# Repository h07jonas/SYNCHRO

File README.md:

SYNCHRO
System for Yielding Networked CHannel Rail Operation
SYNCHRO is a modular, high-performance digital model railroad control ecosystem architecture based on the DCC (Digital Command Control) standard. Designed for robust deployment and high signal integrity, the system strictly separates timing and network logic from high-power distribution. Key design pillars include deterministic signal generation, total galvanic isolation to prevent ground loops, and autonomous hardware-level fault management.

System Architecture
The ecosystem is decoupled into three primary hardware modules, allowing independent scaling of logic processing, track driving power, and distributed accessory control.

              +-----------------------------------+
              |      SYNCHRO_Zentrale (MCU)       |
              |  - Timing, Protocol & Networking  |
              +-----------------------------------+
                                |
                                v (Logic Signal / Differential)
              +-----------------------------------+
              |      SYNCHRO_Booster (Power)      |
              |  - Galvanic Isolation (6N137)     |
              |  - Power H-Bridge & Short Control |
              +-----------------------------------+
                                |
                                v (14V DCC Track Power)
              +-----------------------------------+
              |        SYNCHRO_Modul (Acc.)       |
              |  - Signal Monitoring & Decoding   |
              |  - Inductive Load Drivers         |
              +-----------------------------------+
1. Control Unit (SYNCHRO_Zentrale)
The core processing hub handles the network stack, user interface routing, and precision generation of the digital DCC packet stream. It operates entirely on low-voltage logic levels with no direct track-driving capabilities to protect processing assets.

Core Processor: ESP32-S3 microcontroller utilizing its hardware Remote Control (RMT) peripheral engine. This configuration guarantees jitter-free, deterministic DCC bit-timing through dedicated hardware channels, leaving the dual-core CPU free to handle concurrent Wi-Fi, network protocols, and application layer connectivity.

Signal Integrity: Integrated high-speed bus drivers and differential level shifters (MAX485 / 74AHCT125) ensure noise-immune, differential transmission of the logic stream across longer cables to downstream power boosters.

Connectivity: Native USB-C interface providing USB-to-UART bridging for active monitoring, high-rate firmware flashing, and interfacing with industry-standard PC-based railroad command software.

2. Power Booster (SYNCHRO_Booster)
The power-amplification stage isolates the sensitive low-voltage logic signals coming from the Control Unit, scales the voltage rail, and manages high-current output zones to safely drive individual track blocks.

Galvanic Isolation: High-speed 6N137 optocouplers completely break the ground loops between the upstream logic reference ground and the high-current track power ground, preventing destructive feedback currents.

Power Stage: Integrated Full H-Bridge driver (L6203 or discrete N-channel MOSFET bridge layout) optimized to switch high currents at standard track voltages (14V targeted specifically for N-scale layout compliance).

Autonomous Overcurrent Protection: A high-speed hardware-level short-circuit protection loop combining a precision low-side shunt resistor and an analog LM393 comparator. This safety mechanism achieves sub-millisecond latching shutdown independently of MCU firmware involvement, preventing thermal runaway during track shorts.

3. Peripheral Module (SYNCHRO_Modul)
An accessory and function decoder designed to directly tap and monitor the active 14V DCC data stream from the rails, extracting configuration commands to actuate turnouts, mechanical servos, or signal arrays.

Logic Processing: Cost-optimized microcontrollers (ESP32-C3 or ATtiny architectures) coupled with an isolated input filtering stage optimized for reliable track-packet decoding under harsh electronic environments.

Output Driver: High-density, multi-channel Darlington/DMOS transistor arrays (TBD62083AFG / ULN2803A) equipped with integrated clamp diodes to safely absorb inductive flyback voltages generated by heavy turnout switch coils.

Interface Matrix: Universal pin headers and robust terminal blocks customizable via firmware configurations to run solenoid matrix turnouts, static LED signaling displays, or PWM-driven RC servos.

Repository Structure
The directory tree is split logically into engineering domains to facilitate clean version control and modular updates via the graphical Antigravity 2 interface.

SYNCHRO/
├── .gitignore                      # Top-level filter for KiCad/IDE artifacts
├── README.md                       # Core system documentation
├── git_universal_manager.ps1       # Antigravity 2 - Engine
├── Start_Universal_Git_Manager.bat # Antigravity 2 - Launcher
├── Datasheets/                     # Electronic component documentation
├── Docs/                           # System specifications and schematics
├── Software/                       # Source code (Firmware, Apps)
└── Hardware/                       # Electronic Design Automation (EDA)
├── SYNCHRO_Booster/            # KiCad files for Power Booster
├── SYNCHRO_Zentrale/           # KiCad files for Control Unit
└── SYNCHRO_Modul/              # KiCad files for Accessory Decoder

Hardware Development & CAD Rules
All schematics and PCB designs are standardized on KiCad. To prevent repository bloating and synchronization conflicts, adhere strictly to the following tracking protocols:

Versioned Files
*.kicad_pro — Project tracking configurations.

*.kicad_sch — Schematic design worksheets (modular sheet hierarchies are preferred).

*.kicad_pcb — Board layout designs (S-Expression plain text files optimized for line-by-line git diff operations).

Ignored Assets
Local working state files (.kicad_prl), automated schematic backups (-backups/, *.bak), and local editor history configurations (.history/) are systematically excluded via the global .gitignore.

Production assets (Gerber photo-plots, NC drill coordinates, IPC-D-356 netlists, and structural 3D .step files) must be exported exclusively to isolated release packages or tracked explicitly via Git LFS if required.

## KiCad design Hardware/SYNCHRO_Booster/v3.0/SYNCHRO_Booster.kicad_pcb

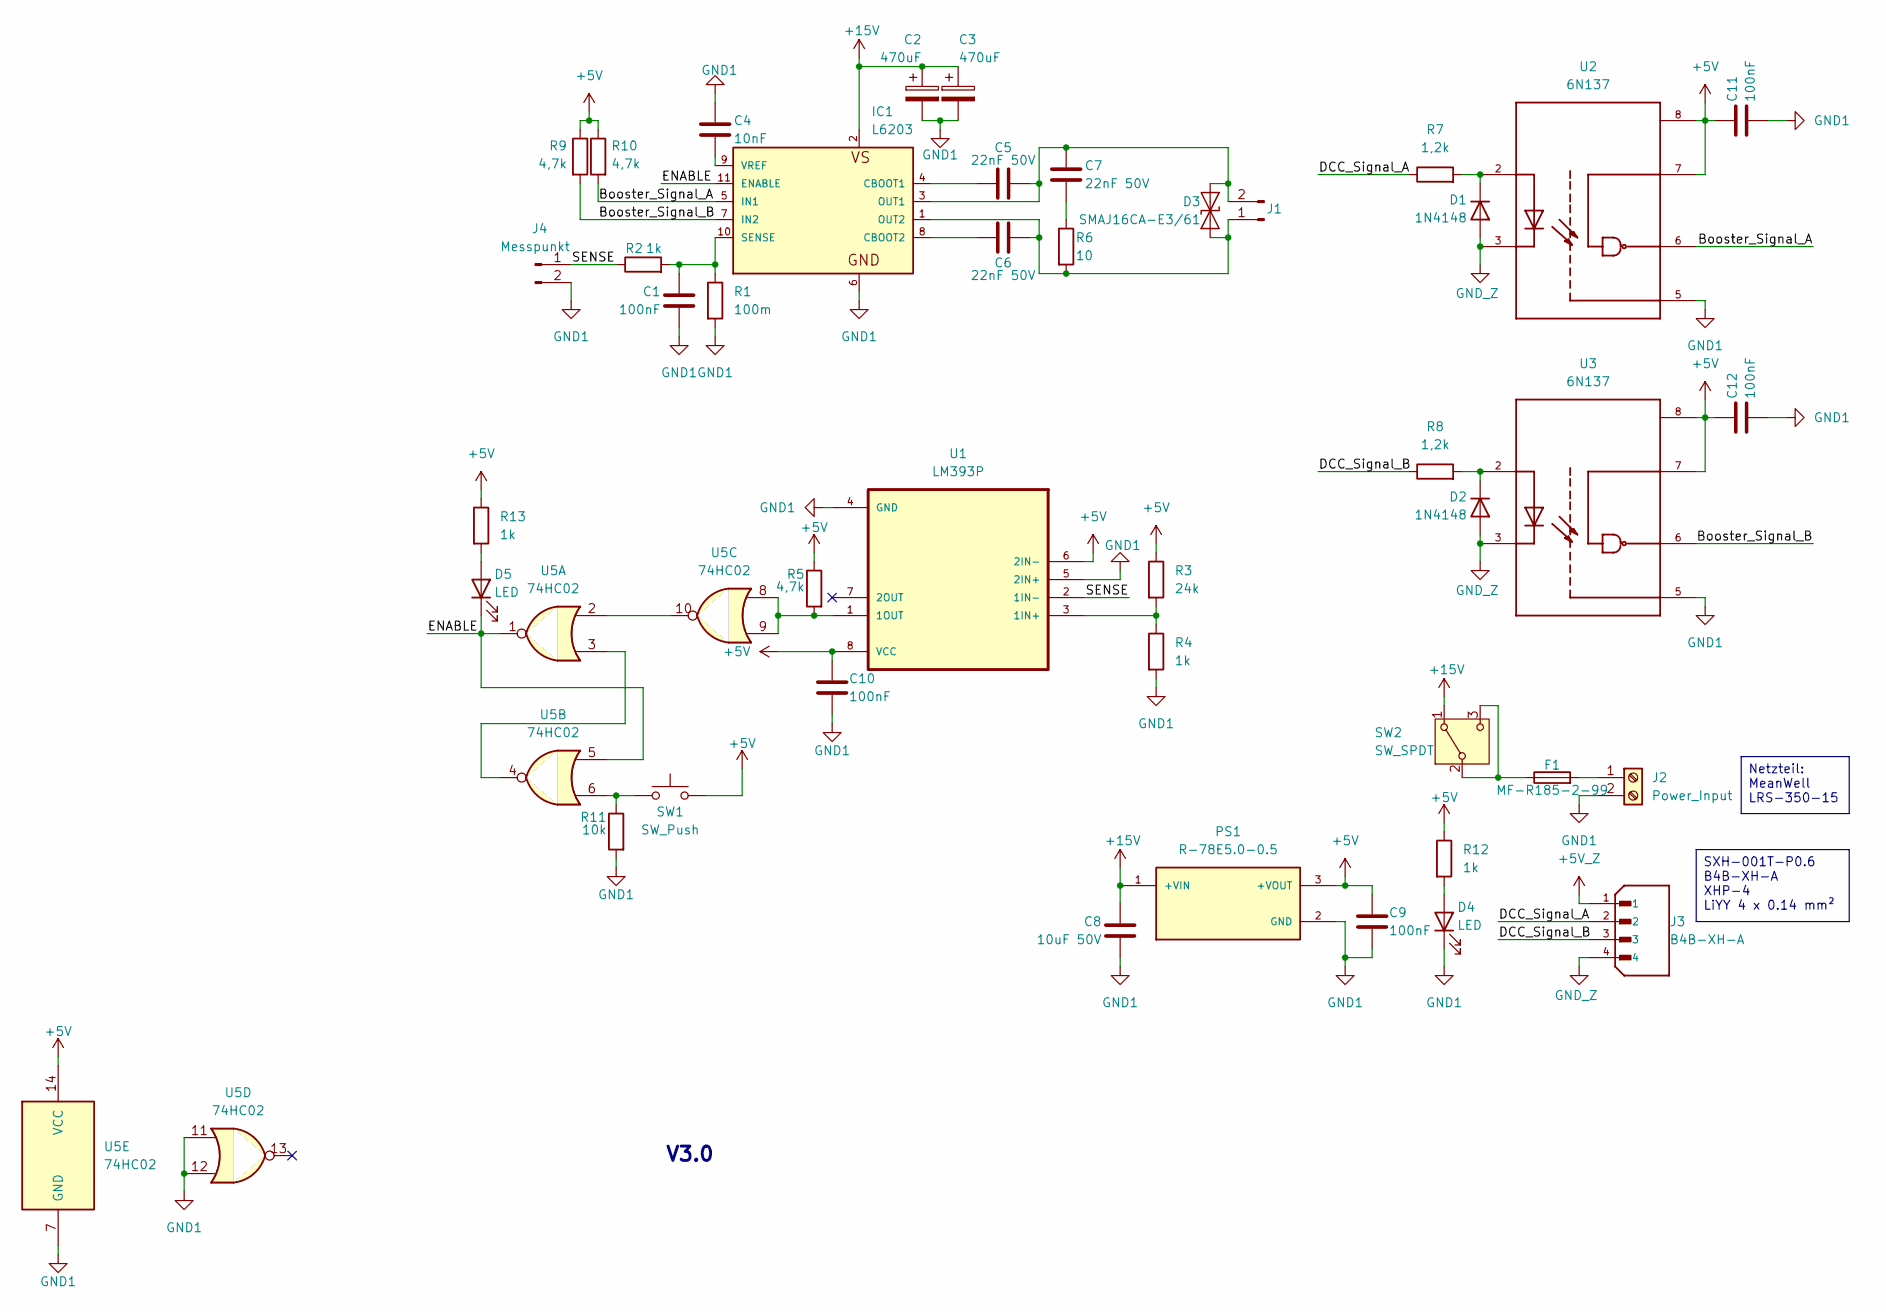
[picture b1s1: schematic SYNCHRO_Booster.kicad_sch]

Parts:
C1, C9, C10, C11, C12: 100nF; C_0603_1608Metric_Pad1.08x0.95mm_HandSolder
C2, C3: 470uF; CP_Radial_D10.0mm_P5.00mm
C4: 10nF; C_Disc_D5.0mm_W2.5mm_P5.00mm
C5, C6, C7: 22nF 50V; C_Rect_L7.0mm_W2.5mm_P5.00mm
C8: 10uF 50V; C_Rect_L7.0mm_W2.5mm_P5.00mm
D1, D2: 1N4148; D_DO-35_SOD27_P7.62mm_Horizontal
D3: SMAJ16CA-E3/61; D_SMA-SMB_Universal_Handsoldering
D4, D5: LED; LED_D5.0mm
F1: MF-R185-2-99; Fuse_Bourns_MF-R185
IC1: L6203; MULTIWATT-11; MPN L6203
J1: Conn_01x02_Pin; TerminalBlock_Phoenix_MKDS-1,5-2-5.08_1x02_P5.08mm_Horizont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
J2: Power_Input; TerminalBlock_Phoenix_MKDS-1,5-2-5.08_1x02_P5.08mm_Horizont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
J3: B4B-XH-A; JST_B4B-XH-A_LF__SN_
J4: Messpunkt; PinHeader_1x02_P2.54mm_Vertical
PS1: R-78E5.0-0.5; CONV_R-78E5.0-0.5; PARTREV 4
R1: 100m; R_2512_6332Metric_Pad1.40x3.35mm_HandSolder
R2, R4, R12, R13: 1k; R_0805_2012Metric_Pad1.20x1.40mm_HandSolder
R3: 24k; R_0805_2012Metric_Pad1.20x1.40mm_HandSolder
R5, R9, R10: 4,7k; R_0805_2012Metric_Pad1.20x1.40mm_HandSolder
R6: 10; R_0805_2012Metric_Pad1.20x1.40mm_HandSolder
R7, R8: 1,2k; R_0805_2012Metric_Pad1.20x1.40mm_HandSolder
R11: 10k; R_0805_2012Metric_Pad1.20x1.40mm_HandSolder
SW1: SW_Push; SW_PUSH_6mm
SW2: SW_SPDT; TerminalBlock_Phoenix_MKDS-3-3-5.08_1x03_P5.08mm_Horizontal
U1: LM393P; DIP762W50P254L977H451Q8
U2, U3: 6N137; DIP762W50P254L977H451Q8
U5: 74HC02; DIP-14_W7.62mm_LongPads

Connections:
+5V: C9.1, C10.1, C11.1, C12.1, PS1.3 (+VOUT), R3.1, R5.1, R9.1, R10.1, R12.1, R13.1, SW1.1, U1.6 (2IN-), U1.8 (VCC), U2.7, U2.8, U3.7, U3.8, U5.14 (VCC)
+5V_Z: J3.1
+15V: C2.1, C3.1, C8.1, IC1.2, PS1.1 (+VIN), SW2.1 (A)
/Booster_Signal_A: IC1.5 (IN1), R10.2, U2.6
/Booster_Signal_B: IC1.7 (IN2), R9.2, U3.6
/DCC_Signal_A: J3.2, R7.1
/DCC_Signal_B: J3.3, R8.1
/ENABLE: D5.1 (K), IC1.11 (ENABLE), U5.1, U5.5
/SENSE: J4.1, R2.1, U1.2 (1IN-)
GND1: C1.2, C2.2, C3.2, C4.1, C8.2, C9.2, C10.2, C11.2, C12.2, D4.1 (K), IC1.6, J2.2, J4.2, PS1.2 (GND), R1.2, R4.2, R11.2, U1.4 (GND), U1.5 (2IN+), U2.5, U3.5, U5.7 (GND), U5.11, U5.12
GND_Z: D1.2 (A), D2.2 (A), J3.4, U2.3, U3.3
unnamed: C7.2, R6.1
unnamed: D1.1 (K), R7.2, U2.2
unnamed: D2.1 (K), R8.2, U3.2
unnamed: C5.2, C7.1, D3.1 (A1), IC1.3 (OUT1), J1.2
unnamed: C6.1, D3.2 (A2), IC1.1 (OUT2), J1.1, R6.2
unnamed: D4.2 (A), R12.2
unnamed: D5.2 (A), R13.2
unnamed: C5.1, IC1.4 (CBOOT1)
unnamed: C6.2, IC1.8 (CBOOT2)
unnamed: C1.1, IC1.10 (SENSE), R1.1, R2.2
unnamed: C4.2, IC1.9 (VREF)
unnamed: F1.2, J2.1
unnamed: R11.1, SW1.2, U5.6
unnamed: F1.1, SW2.2 (B), SW2.3 (C)
unnamed: R3.2, R4.1, U1.3 (1IN+)
unnamed: R5.2, U1.1 (1OUT), U5.8, U5.9
unnamed: U5.3, U5.4
unnamed: U5.2, U5.10

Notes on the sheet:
V3.0
Netzteil: MeanWell LRS-350-15
SXH-001T-P0.6 B4B-XH-A XHP-4 LiYY 4 x 0.14 mm²

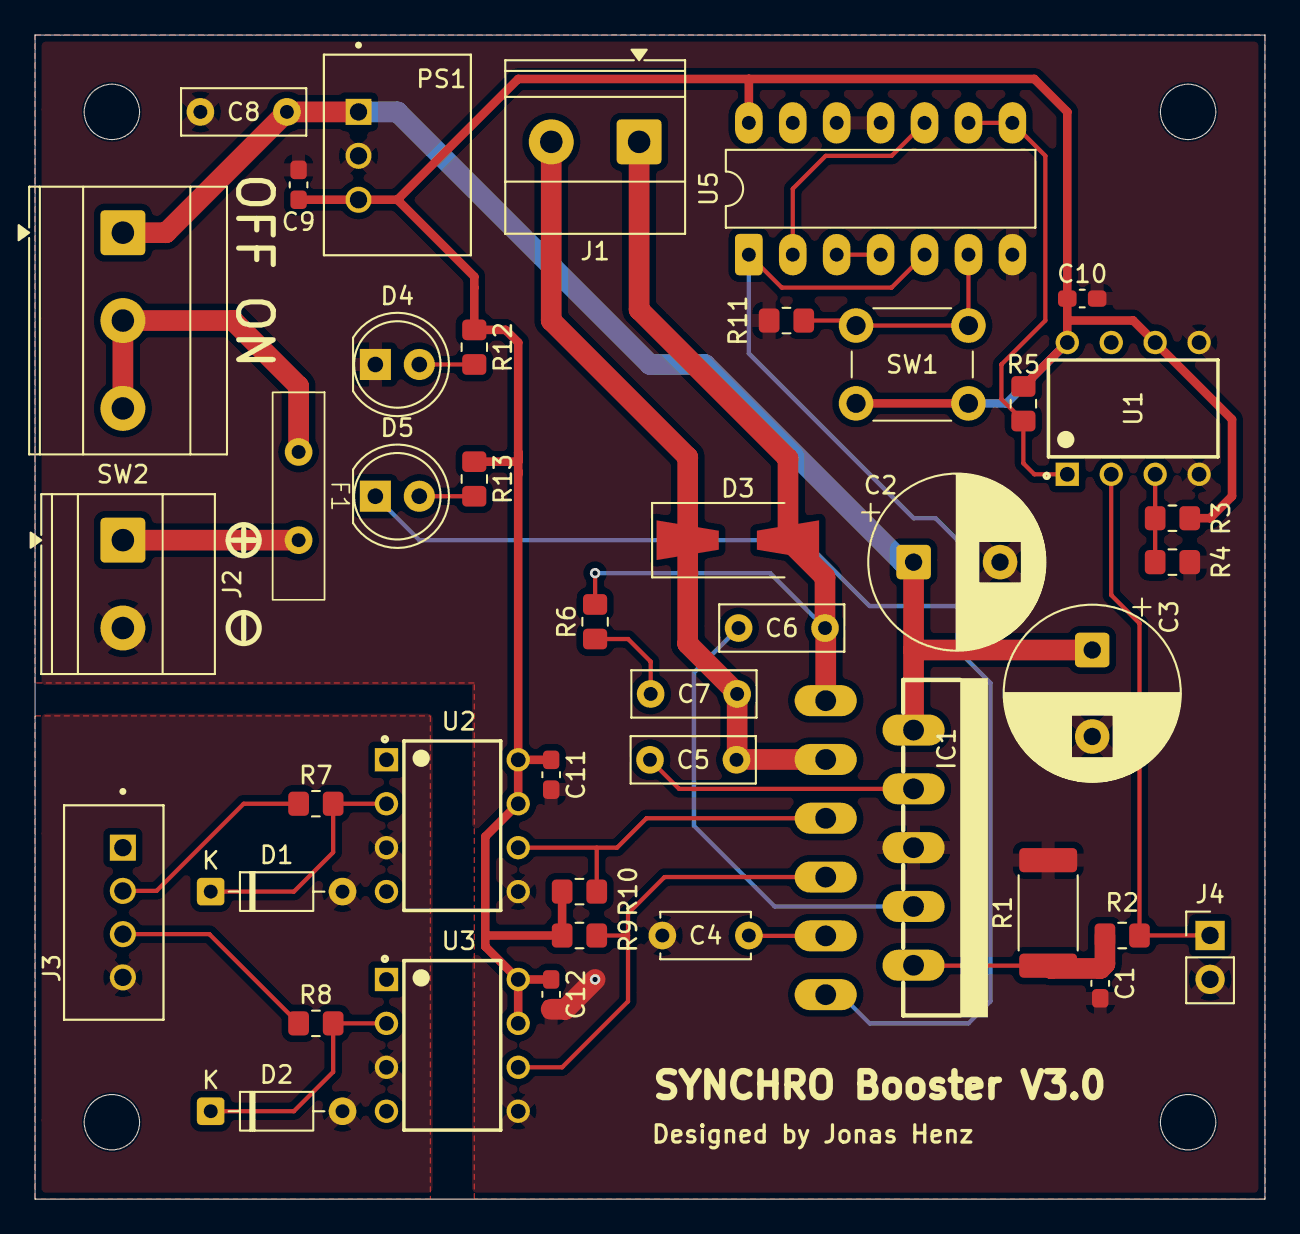
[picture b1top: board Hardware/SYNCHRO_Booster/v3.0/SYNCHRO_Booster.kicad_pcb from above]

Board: 2 copper layers, 71.1 x 67.3 mm, 43 parts (0 on the bottom side), 28 nets.

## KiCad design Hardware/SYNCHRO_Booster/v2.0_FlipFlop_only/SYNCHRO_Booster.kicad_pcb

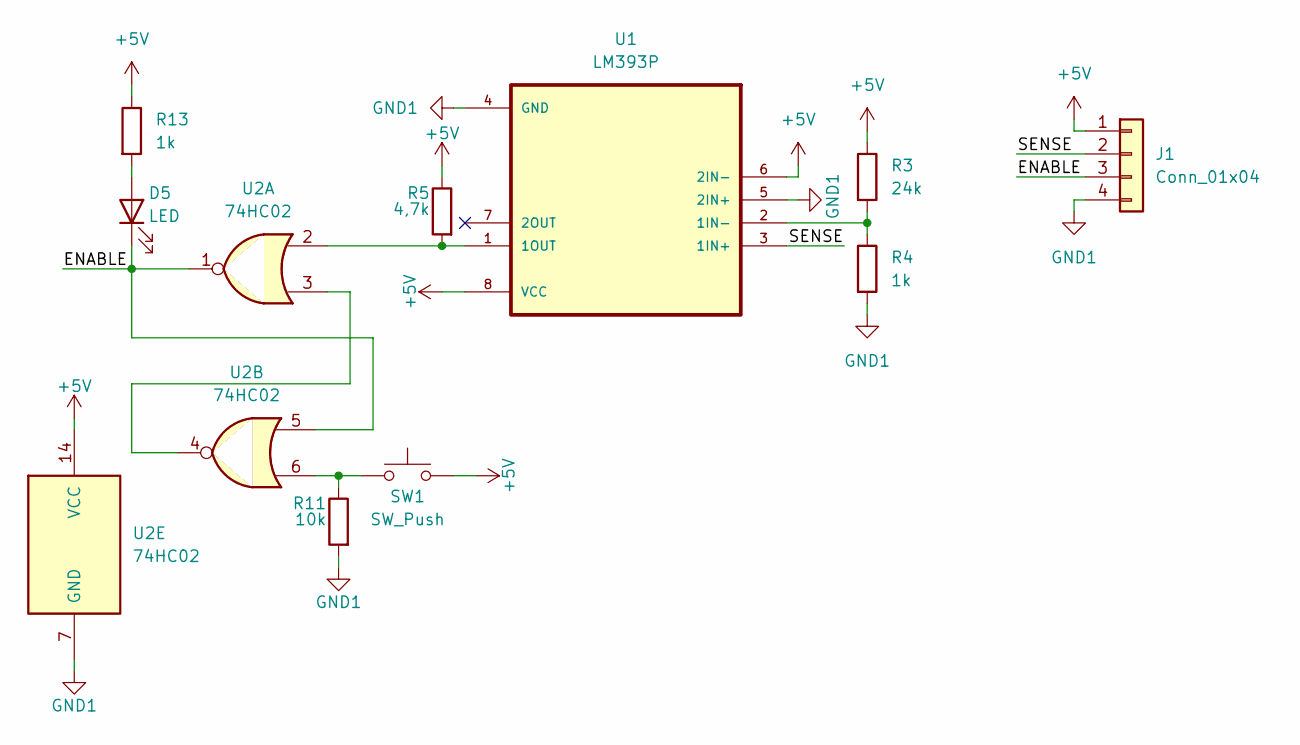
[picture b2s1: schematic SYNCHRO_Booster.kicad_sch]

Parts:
D5: LED; LED_D5.0mm
J1: Conn_01x04; PinSocket_1x04_P2.54mm_Vertical
R3: 24k; R_Axial_DIN0204_L3.6mm_D1.6mm_P7.62mm_Horizontal
R4, R13: 1k; R_Axial_DIN0204_L3.6mm_D1.6mm_P7.62mm_Horizontal
R5: 4,7k; R_Axial_DIN0204_L3.6mm_D1.6mm_P7.62mm_Horizontal
R11: 10k; R_Axial_DIN0204_L3.6mm_D1.6mm_P7.62mm_Horizontal
SW1: SW_Push; SW_PUSH_6mm
U1: LM393P; DIP762W50P254L977H451Q8
U2: 74HC02; DIP-14_W10.16mm_LongPads

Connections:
+5V: J1.1, R3.1, R5.1, R13.1, SW1.1, U1.6 (2IN-), U1.8 (VCC), U2.14 (VCC)
/ENABLE: D5.1 (K), J1.3, U2.1, U2.5
/SENSE: J1.2, U1.3 (1IN+)
GND1: J1.4, R4.2, R11.2, U1.4 (GND), U1.5 (2IN+), U2.7 (GND)
unnamed: D5.2 (A), R13.2
unnamed: R11.1, SW1.2, U2.6
unnamed: R3.2, R4.1, U1.2 (1IN-)
unnamed: R5.2, U1.1 (1OUT), U2.2
unnamed: U2.3, U2.4

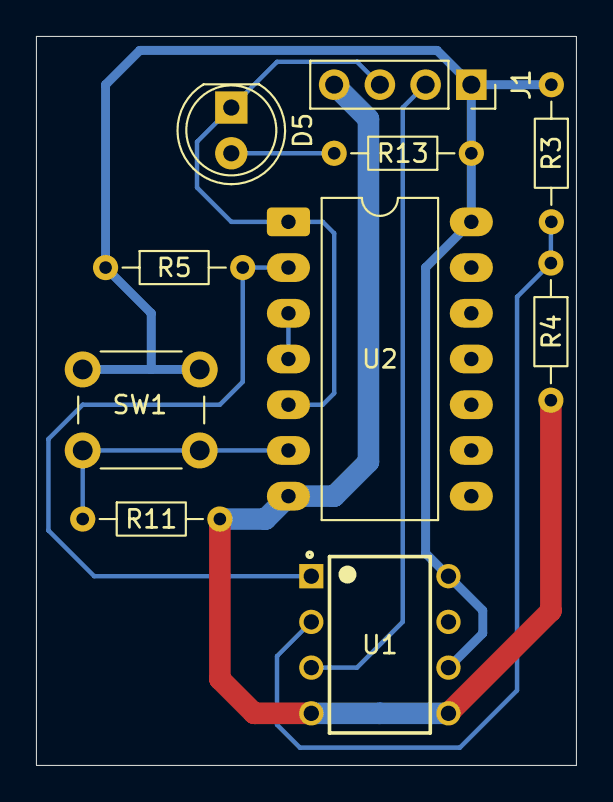
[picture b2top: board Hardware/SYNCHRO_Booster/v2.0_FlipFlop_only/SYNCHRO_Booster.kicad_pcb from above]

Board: 2 copper layers, 30.0 x 40.5 mm, 10 parts (0 on the bottom side), 9 nets.

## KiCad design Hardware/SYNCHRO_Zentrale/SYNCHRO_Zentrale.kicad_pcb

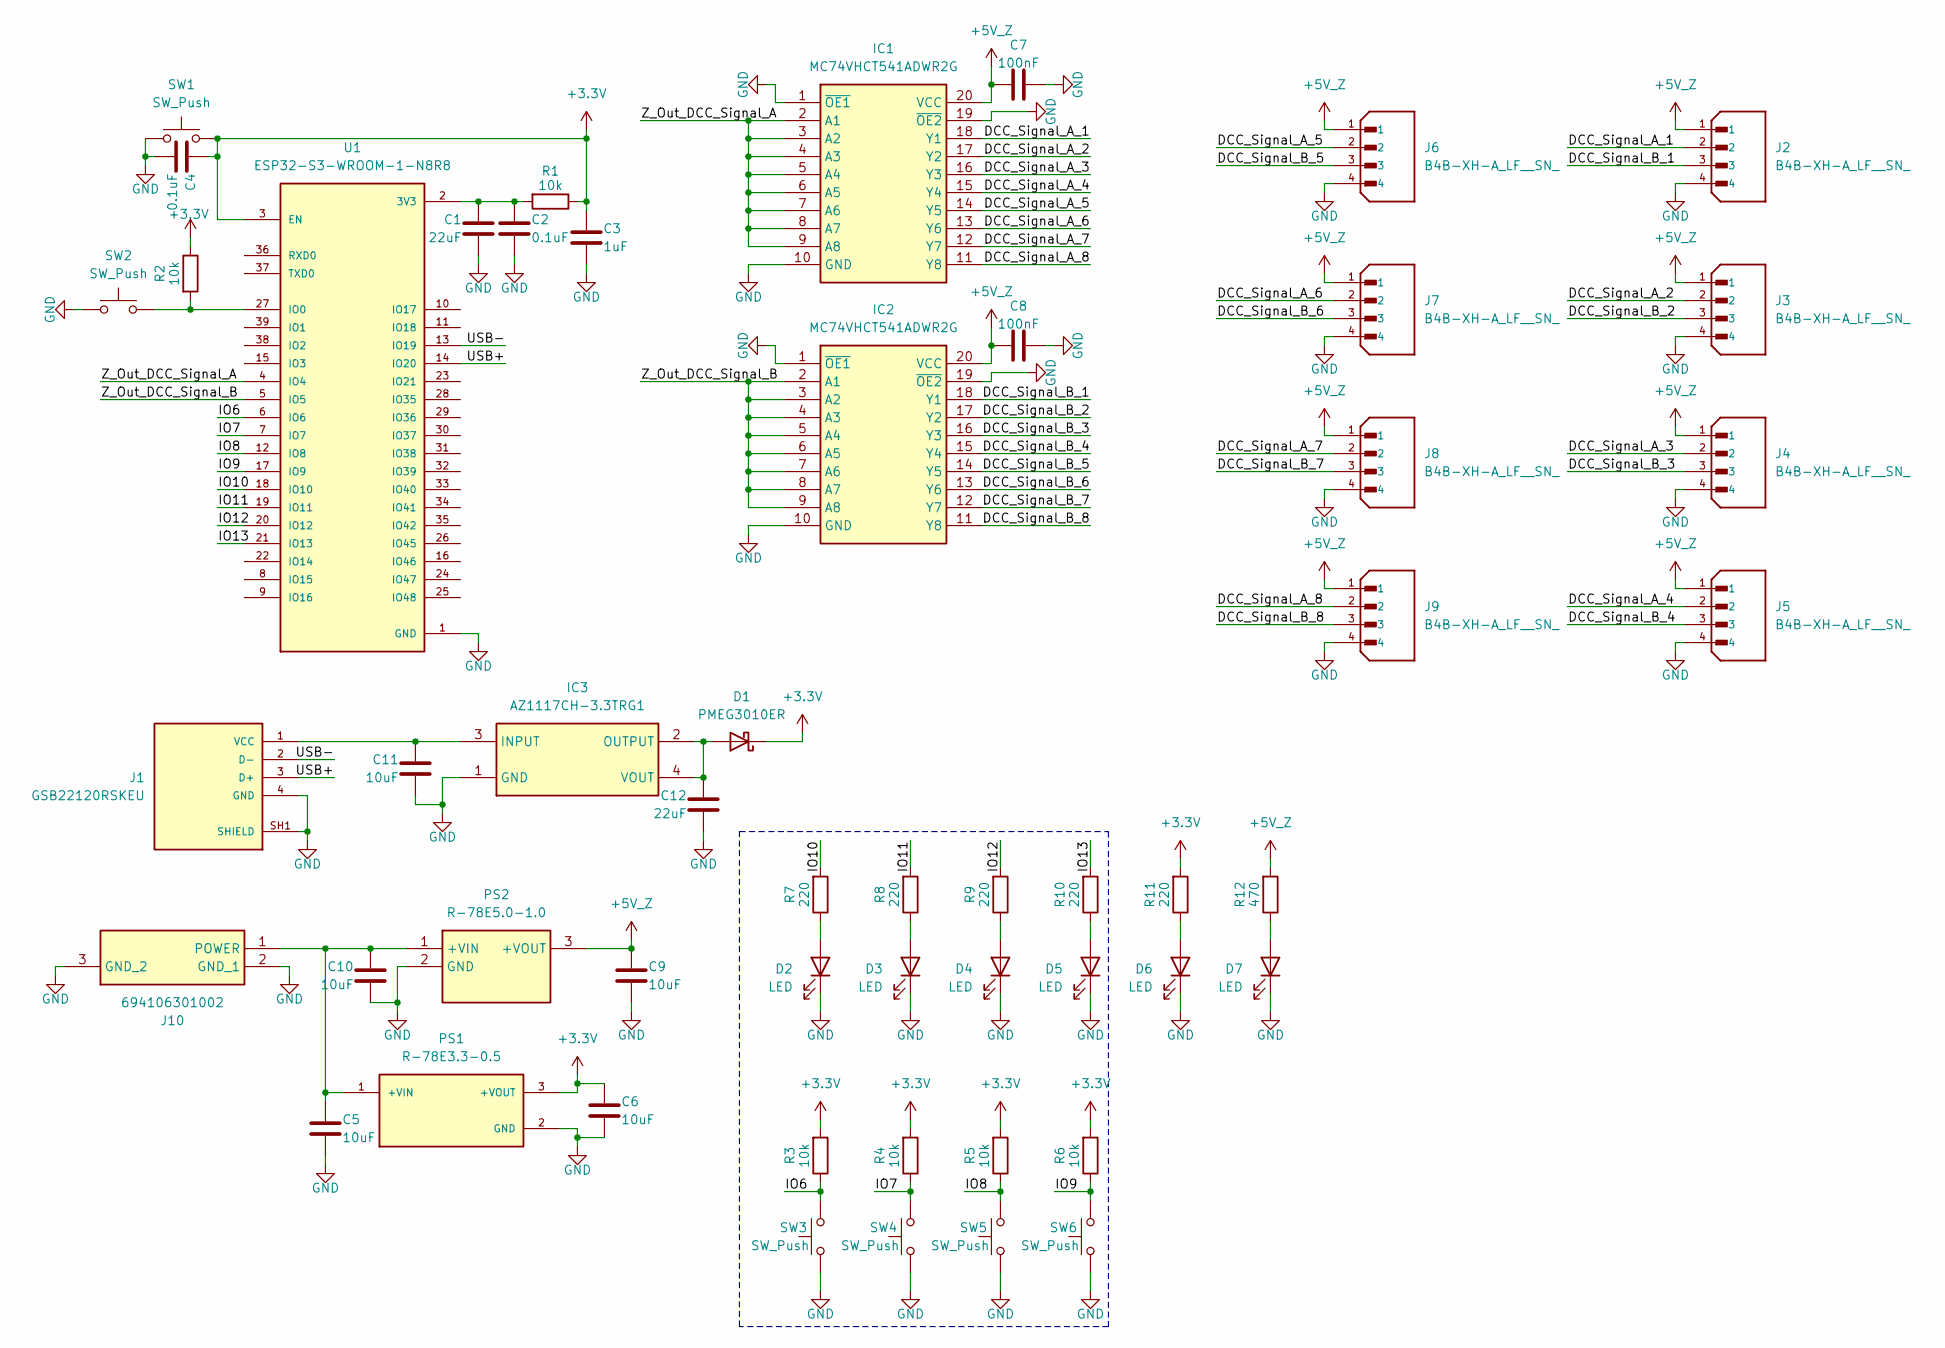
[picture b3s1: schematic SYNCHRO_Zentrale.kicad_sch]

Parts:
C1, C12: 22uF; C_1210_3225Metric_Pad1.33x2.70mm_HandSolder
C2, C4: 0.1uF; C_1206_3216Metric_Pad1.33x1.80mm_HandSolder
C3: 1uF; C_1206_3216Metric_Pad1.33x1.80mm_HandSolder
C5, C6, C9, C10, C11: 10uF; C_1210_3225Metric_Pad1.33x2.70mm_HandSolder
C7, C8: 100nF; C_1206_3216Metric_Pad1.33x1.80mm_HandSolder
D1: PMEG3010ER; Nexperia_CFP3_SOD-123W
D2, D3, D4, D5, D6, D7: LED; LED_D5.0mm
IC1, IC2: MC74VHCT541ADWR2G; SOIC127P1030X265-20N; Manufacturer_Part_Number MC74VHCT541ADWR2G
IC3: AZ1117CH-3.3TRG1; SOT230P700X180-4N; Mouser Part Number 621-AZ1117CH-3.3TRG1
J1: GSB22120RSKEU; AMPHENOL_GSB22120RSKEU; PARTREV E
J2, J3, J4, J5, J6, J7, J8, J9: B4B-XH-A_LF__SN_; JST_B4B-XH-A_LF__SN_
J10: 694106301002; Mouser Part Number 710-694106301002
PS1: R-78E3.3-0.5; CONV_R-78E3.3-0.5; PARTREV 4
PS2: R-78E5.0-1.0; R78E5010; Mouser Part Number 919-R-78E5.0-1.0
R1, R2, R3, R4, R5, R6: 10k; R_0805_2012Metric_Pad1.20x1.40mm_HandSolder
R7, R8, R9, R10, R11: 220; R_0805_2012Metric_Pad1.20x1.40mm_HandSolder
R12: 470; R_0805_2012Metric_Pad1.20x1.40mm_HandSolder
SW1, SW2, SW3, SW4, SW5, SW6: SW_Push; SW_PUSH_6mm
U1: ESP32-S3-WROOM-1-N8R8; ESP32S3WROOM1N8R8

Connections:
+3.3V: C3.1, C4.1, C6.1, D1.1 (K), PS1.3 (+VOUT), R1.1, R2.1, R3.2, R4.2, R5.2, R6.2, R11.2, SW1.2, U1.3 (EN)
+5V_Z: C7.1, C8.1, C9.1, IC1.20 (VCC), IC2.20 (VCC), J2.1, J3.1, J4.1, J5.1, J6.1, J7.1, J8.1, J9.1, PS2.3 (+VOUT), R12.2
/DCC_Signal_A_1: IC1.18 (Y1), J2.2
/DCC_Signal_A_2: IC1.17 (Y2), J3.2
/DCC_Signal_A_3: IC1.16 (Y3), J4.2
/DCC_Signal_A_4: IC1.15 (Y4), J5.2
/DCC_Signal_A_5: IC1.14 (Y5), J6.2
/DCC_Signal_A_6: IC1.13 (Y6), J7.2
/DCC_Signal_A_7: IC1.12 (Y7), J8.2
/DCC_Signal_A_8: IC1.11 (Y8), J9.2
/DCC_Signal_B_1: IC2.18 (Y1), J2.3
/DCC_Signal_B_2: IC2.17 (Y2), J3.3
/DCC_Signal_B_3: IC2.16 (Y3), J4.3
/DCC_Signal_B_4: IC2.15 (Y4), J5.3
/DCC_Signal_B_5: IC2.14 (Y5), J6.3
/DCC_Signal_B_6: IC2.13 (Y6), J7.3
/DCC_Signal_B_7: IC2.12 (Y7), J8.3
/DCC_Signal_B_8: IC2.11 (Y8), J9.3
/IO6: R3.1, SW3.2, U1.6 (IO6)
/IO7: R4.1, SW4.2, U1.7 (IO7)
/IO8: R5.1, SW5.2, U1.12 (IO8)
/IO9: R6.1, SW6.2, U1.17 (IO9)
/IO10: R7.2, U1.18 (IO10)
/IO11: R8.2, U1.19 (IO11)
/IO12: R9.2, U1.20 (IO12)
/IO13: R10.2, U1.21 (IO13)
/USB+: J1.3 (D+), U1.14 (IO20)
/USB-: J1.2 (D-), U1.13 (IO19)
/Z_Out_DCC_Signal_A: IC1.2 (A1), IC1.3 (A2), IC1.4 (A3), IC1.5 (A4), IC1.6 (A5), IC1.7 (A6), IC1.8 (A7), IC1.9 (A8), U1.4 (IO4)
/Z_Out_DCC_Signal_B: IC2.2 (A1), IC2.3 (A2), IC2.4 (A3), IC2.5 (A4), IC2.6 (A5), IC2.7 (A6), IC2.8 (A7), IC2.9 (A8), U1.5 (IO5)
GND: C1.2, C2.2, C3.2, C4.2, C5.2, C6.2, C7.2, C8.2, C9.2, C10.2, C11.2, C12.2, D2.1 (K), D3.1 (K), D4.1 (K), D5.1 (K), D6.1 (K), D7.1 (K), IC1.1 (~OE1), IC1.10 (GND), IC1.19 (~OE2), IC2.1 (~OE1), IC2.10 (GND), IC2.19 (~OE2), IC3.1 (GND), J1.4 (GND), J1.SH1 (SHIELD), J1.SH2 (SHIELD), J2.4, J3.4, J4.4, J5.4, J6.4, J7.4, J8.4, J9.4, J10.2 (GND_1), J10.3 (GND_2), PS1.2 (GND), PS2.2 (GND), SW1.1, SW2.1, SW3.1, SW4.1, SW5.1, SW6.1, U1.1 (GND), U1.40 (GND), U1.41_1 (GND), U1.41_2 (GND), U1.41_3 (GND), U1.41_4 (GND), U1.41_5 (GND), U1.41_6 (GND), U1.41_7 (GND), U1.41_8 (GND), U1.41_9 (GND)
unnamed: C12.1, D1.2 (A), IC3.2 (OUTPUT), IC3.4 (VOUT)
unnamed: D2.2 (A), R7.1
unnamed: D3.2 (A), R8.1
unnamed: D4.2 (A), R9.1
unnamed: D5.2 (A), R10.1
unnamed: D6.2 (A), R11.1
unnamed: D7.2 (A), R12.1
unnamed: C11.1, IC3.3 (INPUT), J1.1 (VCC)
unnamed: C5.1, C10.1, J10.1 (POWER), PS1.1 (+VIN), PS2.1 (+VIN)
unnamed: C1.1, C2.1, R1.2, U1.2 (3V3)
unnamed: R2.2, SW2.2, U1.27 (IO0)

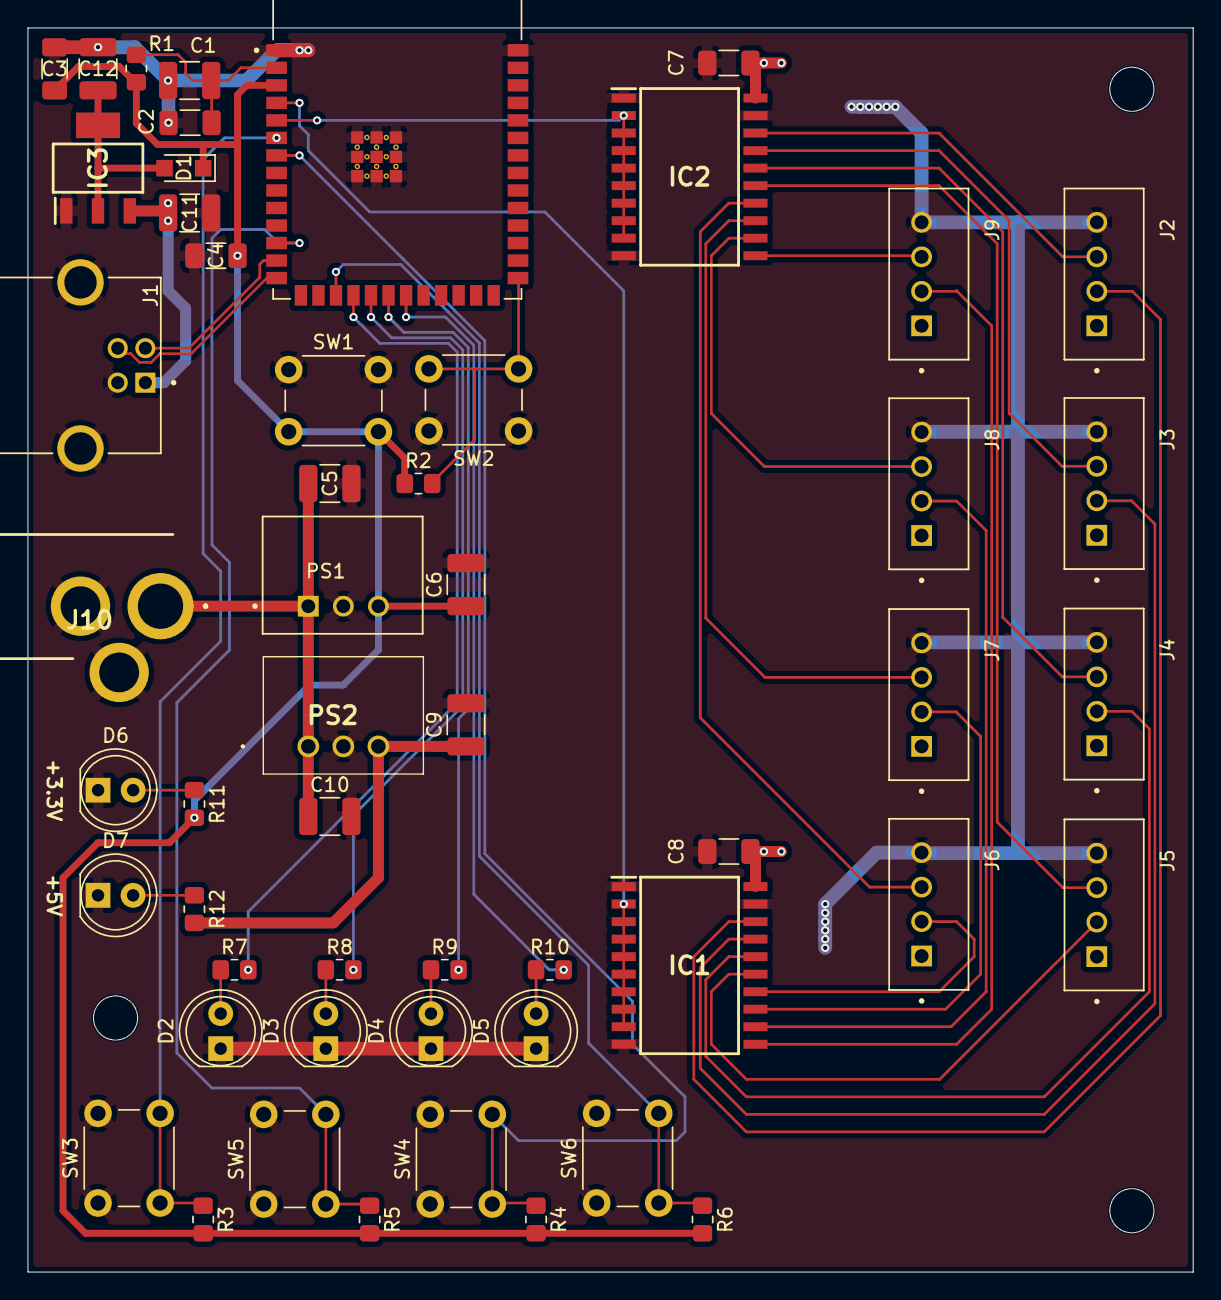
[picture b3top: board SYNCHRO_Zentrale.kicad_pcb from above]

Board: 2 copper layers, 84.5 x 90.2 mm, 53 parts (0 on the bottom side), 42 nets.

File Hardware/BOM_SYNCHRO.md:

|**Name**|**Anzahl**|**Bestellnummer**|**Lieferant**|
|-|-|-|-|
|ESP32-S3-WROOM1-N8R8|1|356-EP32S3WROOM1N8R8|mouser|
|Keramikkondensator 0.1uF X7R 1206|1|77-VJ1206Y104KXXMT|mouser|
|Keramikkondensator 1uF X7R 1206|1|77-VJ1206Y105KLXAJ32|mouser|
|Keramikkondensator 22uF X7R 1210|1|963-MAAST32MSB7226MP|mouser|
|Dickfilmwiderstände SMD 0805 1% 10kOhms 1/8W|2|603-RE0805FRE1010KL|mouser|
|USB 2.0 B Type|1|523-GSB22120RSKEU|mouser|
|DC/DC-Wandler – Durchsteckmontage 3.3V 500mA|1|919-R-78E3.3-0.5|mouser|
|Keramikkondensator 10uF X7R 1210|1|963-TMK325AB7106KMPR|mouser|
|Leitungstreiber Non-inverting Octal Bus|2|863-C74VHCT541ADWR2G|mouser|
|DC/DC-Wandler – Durchsteckmontage 8-28Vin 5V 1.0A THRU|1|919-R-78E5.0-1.0|mouser|
|AC-Adapter 12V 1A|1|490-SWI12-12-E-P5|mouser|
|DC-Spannungsversorgungssteckverbinder|1|710-694106301002|mouser|
|LDO Spannungs-Regulator LDO BJT HiCurr 3.3V 1A|1|621-AZ1117CH-3.3TRG1|mouser|
|Schottky Diode|1|771-PMEG3010ER-QX|mouser|
|XH Header Sockel|8|306-B4BXHALFSN|mouser|

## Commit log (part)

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2026-06-12 Migration: Neue professionelle Projektstruktur auf OneDrive eingerichtet
2026-06-12 git-manager
2026-06-12 Fix: .gitkeep Platzhalter fuer Software, Docs und Datasheets hinzugefuegt
2026-06-12 bug fix
2026-06-12 kicad-library push
2026-06-12 bug fix [main]
2026-06-12 first draft
2026-06-12 Add .gitignore and untrack temp lockfiles
2026-06-12 Fix potential GUI freeze by adding --no-edit to merge and pull
2026-06-12 git manager bug fix
2026-06-12 Remove unused debug script
2026-06-12 adding components
2026-06-12 designing-backup
2026-06-17 RJ45-Connection to booster
2026-06-17 Add robust ahead/behind check and push-only mode to git manager
2026-06-17 general push test
2026-06-21 Booster Schematic Update
2026-06-26 Updating design with RS-FlipFlop
